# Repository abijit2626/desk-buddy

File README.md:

# Dewy, the desk buddy

Dewy is a little robot that lives on a desk. It blinks, looks around, gets bored, naps and wakes up with new
eyes. You play with it by touching and moving it, and it keeps you company with study timers, reminders, the
weather and notes sent from far away.

Dewy runs on an ESP32-S3 with a 3.2" touch screen and a motion sensor in a 3D-printed case. A small Cloudflare
server and a phone app connect it to the internet. I'm building it as a gift and as my TinkerHub scholarship
project. Follow along in the [build log](docs/BUILD_LOG.md).

> **Status (17 Nov 2026):** the face, touch, motion, Wi-Fi and the cloud all work on the real board. Voice
> (mic, speaker and the "Hey Dewy" wake word on the board) is next, and the parts arrive on 20 Nov. The
> prototype is due on 30 Nov.

## What it does

| | |
|---|---|
| **A face that's alive** | 12 moods, blinking, glancing around and breathing, drawn from scratch at about 50 frames a second. New eye colours (46 sets, some rare) and pupil shapes every time it wakes |
| **Touch** | Poke it and it squints; poke it 5 times and it gets grumpy; hold a finger on it and it blushes |
| **Motion** | Shake it (dizzy spiral eyes), pick it up (surprised), lean it (the eyes roll downhill), lay it face down (quiet time) or turn it upside down ("Flip me back!") |
| **Magic 8-ball** | Tap, then shake within 4 seconds |
| **A bond that grows** | From stranger to friend, close friend, best friend and soulmate. It celebrates each level and misses you when you're away |
| **Helpful bits** | Weather in its eyes (sunglasses, a cloud, rain), a study timer, water and stretch reminders, alarms, a clock and a birthday party |
| **Notes from afar** | Notes sent from a phone pop up on its screen, even from another city |
| **Phone app** | A home-screen web app for timers, alarms, reminders, settings and an on/off switch |
| **Voice** *(coming soon)* | "Hey Dewy" wake word on the board, then a spoken answer: weather, news, the time, notes and timers |

## How it fits together

```mermaid
flowchart LR
  A["Phone app<br/>(home-screen web app)"] -- HTTPS --> W["Cloudflare Worker<br/>+ D1 database"]
  N["Notes link<br/>(another phone)"] -- HTTPS --> W
  D["Dewy<br/>ESP32-S3"] -- "HTTPS sync<br/>every few seconds" --> W
  D -- "voice question" --> W
  W -- "Whisper, chat model,<br/>text to speech" --> AI["Workers AI"]
```

- **Dewy** draws its face on one core, and runs the wake word and network on the other.
- **The Worker** stores settings, queues notes and timers for Dewy, offers firmware updates and answers spoken
  questions. It fits in Cloudflare's free plan.
- **Pairing:** Dewy shows an 8-character code, and the phone app sends it to get its own token. Every token is
  stored only as a hash.

## Hardware

| Part | Notes |
|---|---|
| ESP32-S3-N16R8 dev board | 16 MB flash, 8 MB PSRAM. On some clones the 5V pin only outputs USB power after you bridge the **IN-OUT** pads |
| 3.2" ILI9341 screen, 40-pin (SmartElex) | 8-bit parallel mode (IM2/IM1 to GND, IM0 to 3V3) with XPT2046 resistive touch |
| GY-87 (MPU6050) | Shake, pick-up, tilt, face down and upside down |
| INMP441 microphone, MAX98357A amplifier, small speaker | Voice (being added) |
| 220 µF capacitor | Across the screen's 5 V supply |
| 3D-printed case | [`case/`](case/) |
| Carrier PCB *(v0.1, not yet made)* | [`pcb/dewy_carrier/`](pcb/dewy_carrier/): every module solders onto one board, with no loose wires |

Full pin tables are in [`firmware/dewy/config.h`](firmware/dewy/config.h) and
[`firmware/README.md`](firmware/README.md).

## Repository

| Folder | What's in it |
|---|---|
| [`firmware/`](firmware/) | The Arduino code, PC tests (renders, motion, bond, voice and cloud checks) and a Wokwi simulator copy |
| [`cloud/`](cloud/) | The Cloudflare Worker, its database migrations, the phone app and end-to-end tests |
| [`voice/wakeword/`](voice/wakeword/) | Training the "Hey Dewy" wake word (microWakeWord) and the trained model |
| [`case/`](case/) | Printable STL files and the scripts that make them |
| [`pcb/dewy_carrier/`](pcb/dewy_carrier/) | The carrier board: KiCad file, Gerbers and the scripts that place and route it |
| [`docs/`](docs/) | The illustrated manual and the [build log](docs/BUILD_LOG.md) |

## Build your own

1. **Firmware:** follow [`firmware/README.md`](firmware/README.md). It covers the Arduino IDE or `arduino-cli`
   with the ESP32 core 3.3, OPI PSRAM, 16 MB flash, and the `SCREEN_PARALLEL` build flag.
2. **Private settings:** copy `firmware/dewy/secrets.example.h` to `secrets.h`. Git never uploads that file.
3. **Server and app (optional):** follow [`cloud/README.md`](cloud/README.md). It takes about 10 minutes on a free
   Cloudflare account.
4. **Wake word (optional):** see [`voice/wakeword/README.md`](voice/wakeword/README.md). Training runs on an
   NVIDIA GPU under WSL2.

Tests: `bash firmware/test/run_tests.sh` (firmware, on a PC), and `npm test` in `cloud/` with `npm run dev`
running.

## Licence

Dewy is free to build, study, change and share for **non-commercial** use. Please don't sell it, or sell things
made from it.

- **Code** (firmware, cloud, tools, scripts): [PolyForm Noncommercial 1.0.0](LICENSE)
- **Designs and docs** (`case/`, `pcb/`, `docs/`): [CC BY-NC 4.0](LICENSES/CC-BY-NC-4.0.txt)
- **Third-party parts keep their own licences:** see [NOTICE.md](NOTICE.md). The wake word model is for
  personal, non-commercial use, because some of the sounds it was trained on are licensed that way.

Made by Abijit Arun ([@abijit2626](https://github.com/abijit2626)).

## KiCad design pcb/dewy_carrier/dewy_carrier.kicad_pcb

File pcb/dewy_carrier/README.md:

# Dewy carrier board v0.1

A 2-layer 99.7 x 66 mm board that sits 11 mm behind the screen, inside the v2 case. Every module is
soldered to it, so there are no jumper wires. Only through-hole parts.

## Files
- `gerbers/` (zip: `dewy_carrier_v0.1_gerbers.zip`): upload this to JLCPCB, PCBWay, Lion Circuits or PCB Power.
  Settings: 2 layers, 1.6 mm, HASL, any colour. No assembly.
- `dewy_carrier.kicad_pcb`: the board, opens in KiCad 7 or newer.
- `design.py`: every position and connection; `build.py` places and routes the board; `kicad_out.py` writes the KiCad file
  and runs the design-rule check; `pincheck.py` checks each pin against `firmware/dewy/config.h` and `voice.h`.
  Rebuild: `python3 build.py && python3 kicad_out.py && python3 pincheck.py` (needs KiCad 7's Python module).

## Parts that go on it
| Ref | Part | Face |
|---|---|---|
| J1 | 2x20 female header, 2.54 mm (the screen plugs in here) | screen face |
| U1 | ESP32-S3-N16R8 dev board, through 2 x 22 male pins (holes for both 22.86 mm and 25.4 mm row spacing) | back face |
| U2 | GY-87, 8 pins | back face |
| U3 | MAX98357A, 7 pins; the speaker goes to its own screw terminal | back face |
| J2 | INMP441 mic: 6 short wires (the mic sits at the hole in the top of the case) | back face |
| J3 | 2-pin 5.08 mm screw terminal: 5 V in from the battery/charger board | back face |
| C1 | 220 uF electrolytic, 3.81 mm pitch (the long leg goes in the + hole) | back face |
| H1-H3 | M3 holes for spacers to the screen board | |

## Checked against the real screen (19 Nov)
The SmartElex board measures **91 x 64 mm** (the shop listing says 90 x 55, which is wrong). From the measurements and
a photo of its back (`screen_overlay.png`):
1. **Header direction**: VCC is on the inner row (nearer the middle of the screen board) and at the bottom end, seen
   from the back with the header on the left. `J1_VCC_ROW_OUTER = False`, `J1_VCC_AT_TOP = False`.
2. **Header position**: outer row 2 mm from the screen board's edge, header centred on its 64 mm side.
3. **Standoffs**: H1 and H3 rest on bare board on the screen's back (clear of the SD slot, the chips and the ribbon).
   H2 is on the axis of the screen's top-left corner hole, so one M3 screw can go through both boards.
   Use 11 mm spacers.
4. **The ESP32 board's row spacing**: both spacings are drilled; solder into the row that fits.

The case: its screen fence is 62 mm tall inside, the screen is 64 mm. Sand or file the fence before fitting.

## Power
J3 and the ESP32's 5Vin pin are on the same 5 V line. With the IN-OUT pads bridged, the laptop's USB also feeds
that line, so do not plug the laptop in while the battery board feeds J3. Either switch the battery off while flashing,
or remove the IN-OUT bridge once the battery board powers J3: then J3 powers everything and the laptop's USB
only powers the ESP32.

## Status
Design-rule check: 0 errors, 0 unconnected pads (only silkscreen warnings: the ESP32 outline overhangs the edge on purpose).
Every trace, colour-coded: `connections.png`.
Header and standoff holes checked against the screen's measurements and back photo (see above).

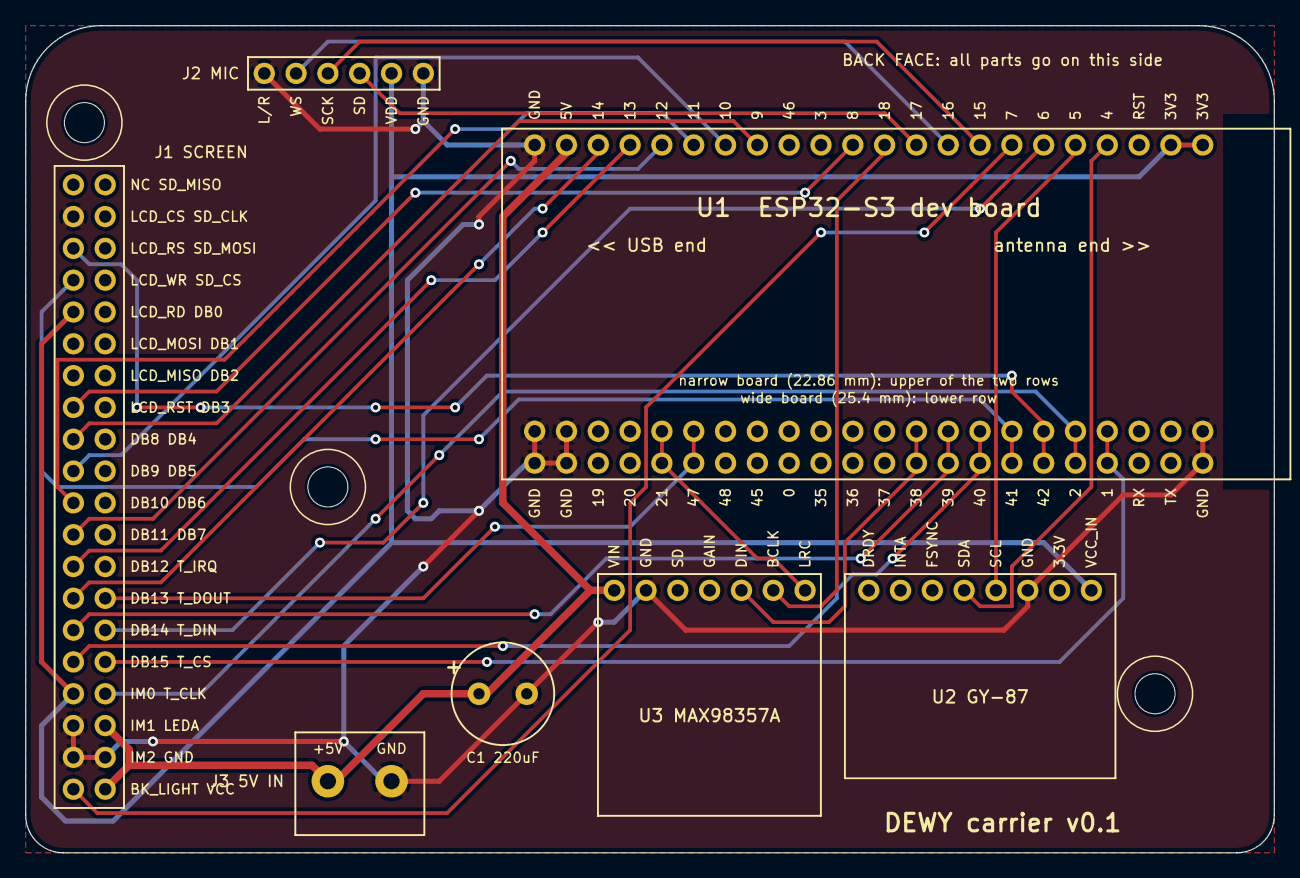
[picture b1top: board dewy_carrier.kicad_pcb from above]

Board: 2 copper layers, 99.7 x 66.0 mm, 10 parts (0 on the bottom side), 27 nets.

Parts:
C1: 220 uF electrolytic
H1, H2, H3: M3 hole
J1: Screen socket 2x20 2.54 mm, soldered on the SCREE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
J2: INMP441 microphone wires
J3: 5 V in screw terminal 5.08 mm
U1: ESP32-S3 dev board (22+22 pins)
U2: GY-87 motion sensor
U3: MAX98357A amplifier

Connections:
+3V3: J1.8 (IM0), J1.32 (LCD_RD), J2.5 (VDD), U1.1 (3V3), U1.2 (3V3), U2.8 (VCC_IN)
+5V: C1.1 (+), J1.1 (VCC), J1.5 (LEDA), J3.1 (+5V), U1.21 (5V), U3.1 (VIN)
AMP_BCLK_GPIO18: U1.11 (18), U3.6 (BCLK)
AMP_DIN_GPIO38: U1.32 (38), U1.54 (38), U3.5 (DIN)
AMP_LRC_GPIO21: U1.40 (21), U1.62 (21), U3.7 (LRC)
BL_GPIO7: J1.2 (BK_LIGHT), U1.7
D0_GPIO9: J1.24 (DB8), U1.15 (9)
D1_GPIO10: J1.22 (DB9), U1.16 (10)
D2_GPIO11: J1.20 (DB10), U1.17 (11)
D3_GPIO12: J1.18 (DB11), U1.18 (12)
D4_GPIO13: J1.16 (DB12), U1.19 (13)
D5_GPIO14: J1.14 (DB13), U1.20 (14)
D6_GPIO39: J1.12 (DB14), U1.31 (39), U1.53 (39)
D7_GPIO40: J1.10 (DB15), U1.30 (40), U1.52 (40)
GND: C1.2 (-), J1.3 (GND), J1.4 (IM2), J1.6 (IM1), J1.38 (LCD_CS), J2.1 (L/R), J2.6 (GND), J3.2 (GND), U1.22 (GND), U1.23 (GND), U1.43 (GND), U1.44 (GND), U1.45 (GND), U1.65 (GND), U1.66 (GND), U2.6 (GND), U3.2 (GND)
LCD_RST_GPIO8: J1.26 (LCD_RST), U1.12 (8)
LCD_RS_GPIO42: J1.36 (LCD_RS), U1.28 (42), U1.50 (42)
LCD_WR_GPIO41: J1.34 (LCD_WR), U1.29 (41), U1.51 (41)
MIC_SCK_GPIO15: J2.3 (SCK), U1.8 (15)
MIC_SD_GPIO17: J2.4 (SD), U1.10 (17)
MIC_WS_GPIO16: J2.2 (WS), U1.9 (16)
SCL_GPIO5: U1.5, U2.5 (SCL)
SDA_GPIO4: U1.4, U2.4 (SDA)
T_CLK_GPIO2: J1.7 (T_CLK), U1.27 (2), U1.49 (2)
T_CS_GPIO1: J1.9 (T_CS), U1.26 (1), U1.48 (1)
T_DIN_GPIO6: J1.11 (T_DIN), U1.6
T_DOUT_GPIO47: J1.13 (T_DOUT), U1.39 (47), U1.61 (47)

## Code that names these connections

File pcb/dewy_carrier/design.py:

"""Dewy carrier board: every position and connection in one place.
Coordinates are the CASE's body coordinates in mm, seen from the BACK of the case (the side the lid closes):
+x to the right, +y up, the screen is behind the board. Board back face (KiCad F.Cu) carries the parts.
"""
G = 0.635                      # routing grid (a quarter of 2.54)

# ---- things to confirm on the real parts before ordering -------------------------------------------------
ESP_ROW_SPACINGS = (22.86, 25.4)   # both hole rows are on the board, so either dev board width fits
J1_VCC_ROW_OUTER = False       # True: the VCC/GND/LEDA row is the one nearer the screen board's edge
J1_VCC_AT_TOP    = False       # True: the VCC end of the header is at the top when the screen is upright
J1_OUTER_X       = -46.19      # where the header's outer row sits in the case (screen pushed into its fence)
J1_CENTRE_Y      = 2.0         # header centred on the screen board's height

# ---- board outline -----------------------------------------------------------------------------------------
X0, X1, Y0, Y1 = -50.0, 49.695, -27.0, 39.04
CORNER_R = 3.0            # bottom corners
CORNER_R_TOP = 6.0        # top corners, rounder so the board slides past the lid posts
def snap(v, o): return o + round((v - o) / G) * G
def sx(v): return snap(v, X0)
def sy(v): return snap(v, Y0)

# ---- screen header J1: 20 columns, each a pair (VCC row, BK_LIGHT row) ----------------------------------------
J1_COLS = [("VCC", "BK_LIGHT"), ("GND", "IM2"), ("LEDA", "IM1"), ("T_CLK", "IM0"), ("T_CS", "DB15"), ("T_DIN", "DB14"),
           ("T_DOUT", "DB13"), ("T_IRQ", "DB12"), ("DB7", "DB11"), ("DB6", "DB10"), ("DB5", "DB9"), ("DB4", "DB8"),
           ("DB3", "LCD_RST"), ("DB2", "LCD_MISO"), ("DB1", "LCD_MOSI"), ("DB0", "LCD_RD"), ("SD_CS", "LCD_WR"),
           ("SD_MOSI", "LCD_RS"), ("SD_CLK", "LCD_CS"), ("SD_MISO", "NC")]
# screen pin -> net (None = not connected)
SCREEN_NET = {"VCC": "+5V", "LEDA": "+5V", "GND": "GND", "BK_LIGHT": "BL_GPIO7", "IM2": "GND", "IM1": "GND", "IM0": "+3V3",
              "LCD_CS": "GND", "LCD_RD": "+3V3", "LCD_RST": "LCD_RST_GPIO8", "LCD_RS": "LCD_RS_GPIO42", "LCD_WR": "LCD_WR_GPIO41",
              "DB8": "D0_GPIO9", "DB9": "D1_GPIO10", "DB10": "D2_GPIO11", "DB11": "D3_GPIO12", "DB12": "D4_GPIO13",
              "DB13": "D5_GPIO14", "DB14": "D6_GPIO39", "DB15": "D7_GPIO40",
              "T_CLK": "T_CLK_GPIO2", "T_CS": "T_CS_GPIO1", "T_DIN": "T_DIN_GPIO6", "T_DOUT": "T_DOUT_GPIO47"}

# ---- ESP32-S3 dev board, lying on its side: antenna to the right, USB to the left ---------------------------
# top row = the dev board's left column (3V3 ... 5Vin, GND), bottom row = its right column (GND, TX ... GND, GND),
# both listed from the antenna end
ESP_TOP = ["3V3", "3V3", "RST", "4", "5", "6", "7", "15", "16", "17", "18", "8", "3", "46", "9", "10", "11", "12", "13", "14", "5V", "GND"]
ESP_BOT = ["GND", "TX", "RX", "1", "2", "42", "41", "40", "39", "38", "37", "36", "35", "0", "45", "48", "47", "21", "20", "19", "GND", "GND"]
ESP_X_FIRST = sx(44.0)          # antenna-end pin
ESP_Y_TOP = sy(29.7)
GPIO_NET = {"3V3": "+3V3", "5V": "+5V", "GND": "GND",
            "4": "SDA_GPIO4", "5": "SCL_GPIO5", "6": "T_DIN_GPIO6", "7": "BL_GPIO7", "15": "MIC_SCK_GPIO15", "16": "MIC_WS_GPIO16",
            "17": "MIC_SD_GPIO17", "18": "AMP_BCLK_GPIO18", "8": "LCD_RST_GPIO8", "9": "D0_GPIO9", "10": "D1_GPIO10", "11": "D2_GPIO11",
            "12": "D3_GPIO12", "13": "D4_GPIO13", "14": "D5_GPIO14", "1": "T_CS_GPIO1", "2": "T_CLK_GPIO2", "42": "LCD_RS_GPIO42",
            "41": "LCD_WR_GPIO41", "40": "D7_GPIO40", "39": "D6_GPIO39", "38": "AMP_DIN_GPIO38", "47": "T_DOUT_GPIO47", "21": "AMP_LRC_GPIO21"}

# ---- modules: (reference, label, first pin x, y, pin names left to right, nets) ---------------------------------
ROW_Y = sy(-6.0)
HEADERS = [
  dict(ref="U2", title="GY-87", x=sx(17.2), y=ROW_Y, pins=["DRDY", "INTA", "FSYNC", "SDA", "SCL", "GND", "3.3V", "VCC_IN"],
       nets=[None, None, None, "SDA_GPIO4", "SCL_GPIO5", "GND", None, "+3V3"], body=(-1.9, 1.3, 19.7, -15.0)),
  dict(ref="U3", title="MAX98357A", x=sx(-3.2), y=ROW_Y, pins=["VIN", "GND", "SD", "GAIN", "DIN", "BCLK", "LRC"],
       nets=["+5V", "GND", None, None, "AMP_DIN_GPIO38", "AMP_BCLK_GPIO18", "AMP_LRC_GPIO21"], body=(-1.3, 1.3, 16.5, -18.0)),
  dict(ref="J2", title="MIC", x=sx(-31.0), y=sy(35.2), pins=["L/R", "WS", "SCK", "SD", "VDD", "GND"],
       nets=["GND", "MIC_WS_GPIO16", "MIC_SCK_GPIO15", "MIC_SD_GPIO17", "+3V3", "GND"], body=None),
]
CAPS = [dict(ref="C1", x=sx(-13.9), y=sy(-14.0), label="220uF")]      # + pad at x, - pad 3.81 to the right
TERMINAL = dict(ref="J3", x=sx(-26.0), y=sy(-21.0), label="5V IN")    # +5V pad at x, GND pad 5.08 to the right
# M3 standoff holes, checked against a photo of the screen's back (screen 91 x 64 mm, header 2 mm from its edge):
# H1 and H3 rest on bare board; H2 is on the axis of the screen's own top-left corner hole, so one screw can go through both.
HOLES = [(sx(40.0), sy(-14.0)), (-45.31, 31.30), (sx(-26.0), sy(2.0))]
ANTENNA_KEEPOUT = (45.6, 2.0, 50.0, 32.0)   # no copper under the ESP32's antenna

def j1_pads():
    """[(name, net, x, y)] for the 40 screen pins"""
    out = []
    inner_x = J1_OUTER_X + 2.54
    for c, (a, b) in enumerate(J1_COLS):
        y = J1_CENTRE_Y + (9.5 - c) * 2.54 * (1 if J1_VCC_AT_TOP else -1)
        xa, xb = (J1_OUTER_X, inner_x) if J1_VCC_ROW_OUTER else (inner_x, J1_OUTER_X)
        out.append((a, SCREEN_NET.get(a), sx(xa), sy(y))); out.append((b, SCREEN_NET.get(b), sx(xb), sy(y)))
    return out
def esp_pads():
    out = []
    for i, n in enumerate(ESP_TOP): out.append((n, GPIO_NET.get(n), ESP_X_FIRST - i * 2.54, ESP_Y_TOP, "top"))
    for sp in ESP_ROW_SPACINGS:
        for i, n in enumerate(ESP_BOT): out.append((n, GPIO_NET.get(n), ESP_X_FIRST - i * 2.54, sy(ESP_Y_TOP - sp), "bot%.2f" % sp))
    return out
